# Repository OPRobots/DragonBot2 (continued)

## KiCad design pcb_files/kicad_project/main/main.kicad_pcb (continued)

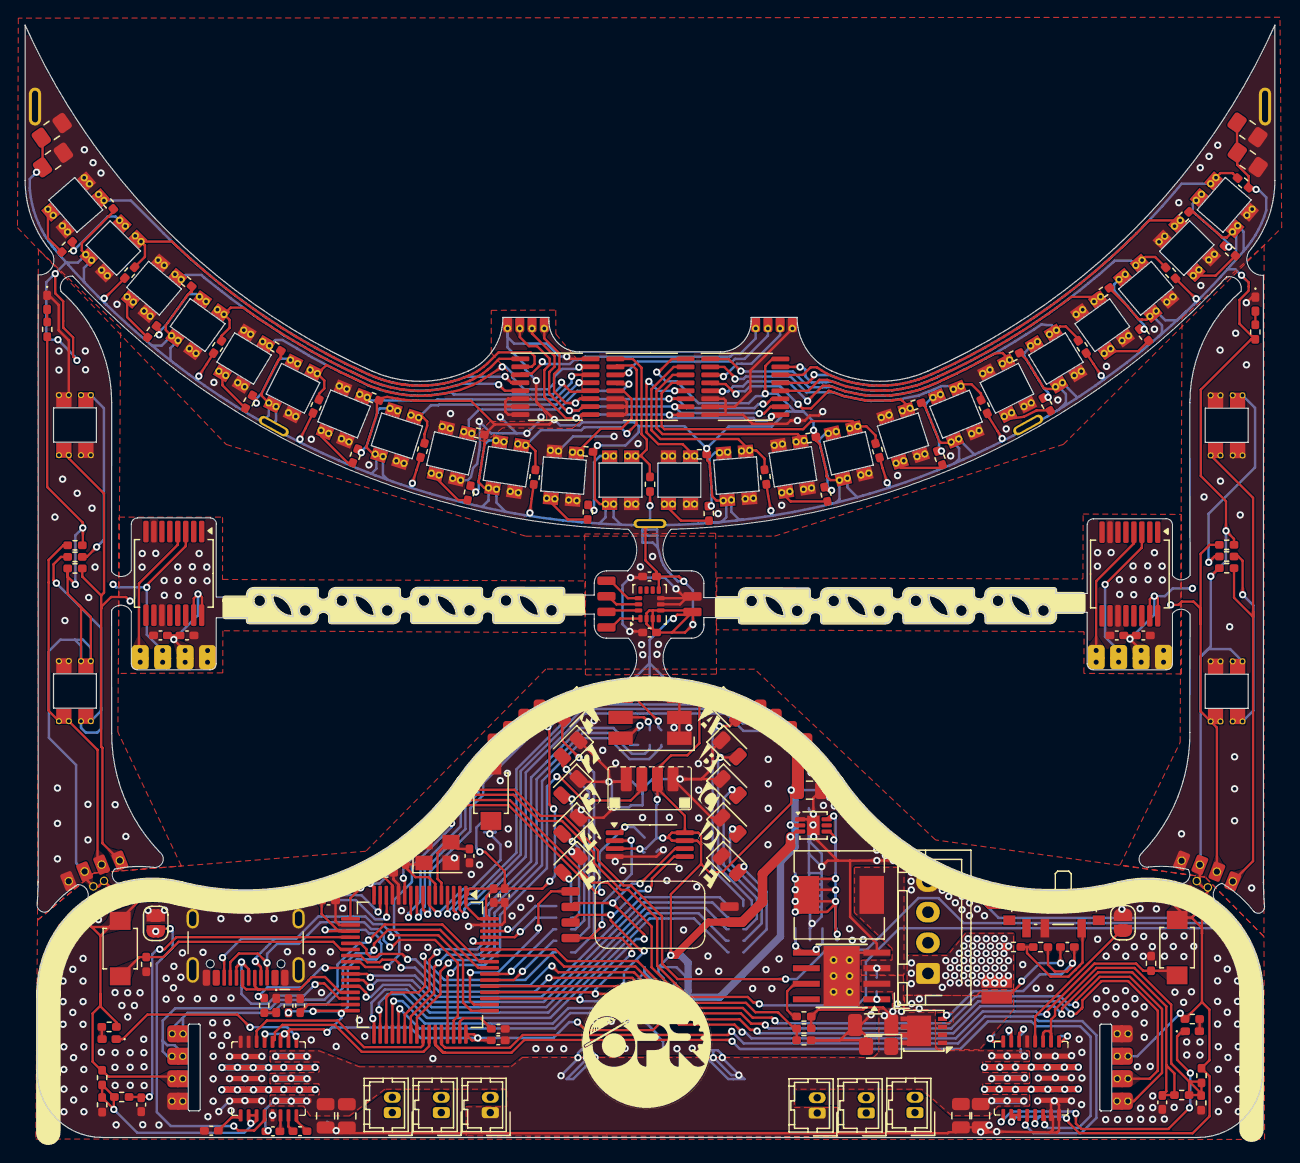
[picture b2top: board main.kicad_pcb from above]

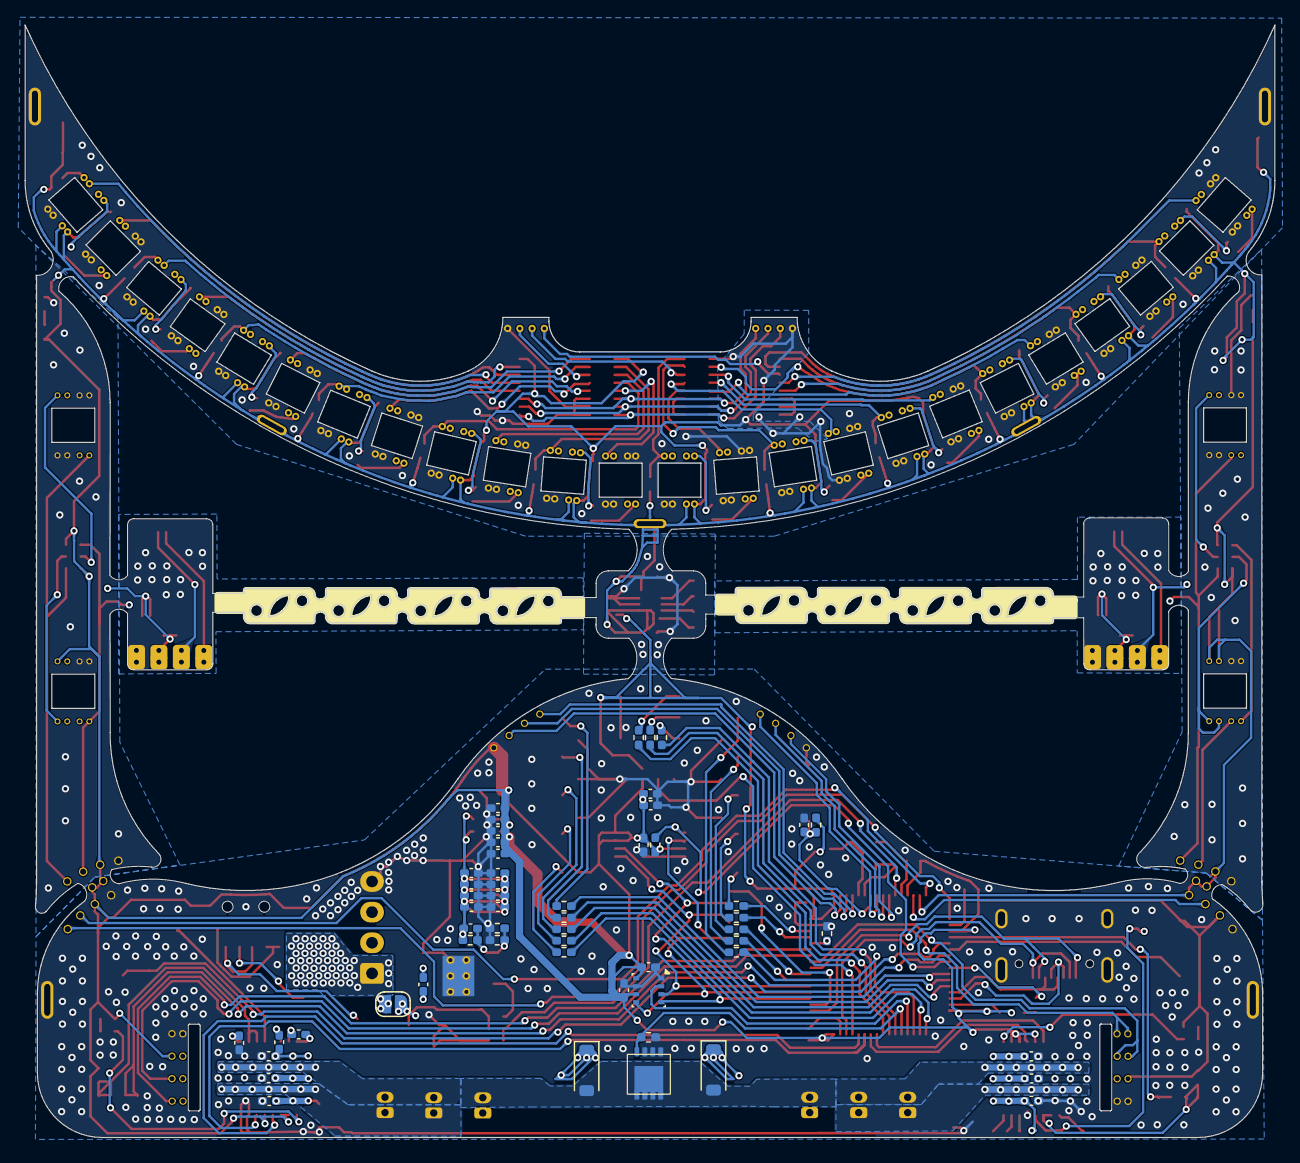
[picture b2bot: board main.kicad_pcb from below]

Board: 2 copper layers, 102.0 x 90.8 mm, 250 parts (56 on the bottom side), 186 nets.

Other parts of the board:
JP99: SolderJumper_2_Open; SolderJumper-2_P1.3mm_Open_RoundedPad1.0x1.5mm
kibuzzard-6A86F9E9: G***; kibuzzard-6A86F9E9
kibuzzard-6A86F9FA: G***; kibuzzard-6A86F9FA
kibuzzard-6A86FA0A: G***; kibuzzard-6A86FA0A
kibuzzard-6A86FA24: G***; kibuzzard-6A86FA24
kibuzzard-6A86FA32: G***; kibuzzard-6A86FA32
kibuzzard-6A86FBBC: G***; kibuzzard-6A86FBBC
kibuzzard-6A86FBC4: G***; kibuzzard-6A86FBC4
kibuzzard-6A86FBCD: G***; kibuzzard-6A86FBCD
kibuzzard-6A86FBEE: G***; kibuzzard-6A86FBEE
kibuzzard-6A86FBF6: G***; kibuzzard-6A86FBF6

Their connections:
/3.3_MPU: JP99.1 (A); also elsewhere on the board

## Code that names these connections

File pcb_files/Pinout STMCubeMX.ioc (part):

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Mcu.Name=STM32F405RGTx
Mcu.Package=LQFP64
Mcu.UserName=STM32F405RGTx
PA0-WKUP.GPIOParameters=GPIO_Label
PA0-WKUP.GPIO_Label=IN_MARK_L1
PA0-WKUP.Signal=ADCx_IN0
PA1.GPIOParameters=GPIO_Label
PA1.GPIO_Label=IN_MARK_L2
PA1.Signal=ADCx_IN1
PA10.GPIOParameters=GPIO_Label
PA10.GPIO_Label=PWM_MOT_L_B
PA10.Signal=S_TIM1_CH3
PA11.GPIOParameters=GPIO_Label
PA11.GPIO_Label=PWM_MOT_L_A
PA11.Signal=S_TIM1_CH4
PA12.GPIOParameters=GPIO_Label
PA12.GPIO_Label=IR_SENSOR
PA12.Signal=GPXTI12
PA13.Signal=SYS_JTMS-SWDIO
PA14.Signal=SYS_JTCK-SWCLK
PA15.GPIOParameters=GPIO_Label
PA15.GPIO_Label=SPI_NSS_MPU
PA15.Signal=GPIO_Output
PA2.GPIOParameters=GPIO_Label
PA2.GPIO_Label=IN_MARK_L3
PA2.Signal=ADCx_IN2
PA3.GPIOParameters=GPIO_Label
PA3.GPIO_Label=IN_MARK_R1
PA3.Signal=ADCx_IN3
PA4.GPIOParameters=GPIO_Label
PA4.GPIO_Label=IN_MARK_R2
PA4.Signal=ADCx_IN4
PA5.GPIOParameters=GPIO_Label
PA5.GPIO_Label=IN_MARK_R3
PA5.Signal=ADCx_IN5
PA6.GPIOParameters=GPIO_Label
PA6.GPIO_Label=IN_CURR_ML
PA6.Signal=ADCx_IN6
PA7.GPIOParameters=GPIO_Label
PA7.GPIO_Label=IN_CURR_MR
PA7.Signal=ADCx_IN7
PA8.GPIOParameters=GPIO_Label
PA8.GPIO_Label=PWM_MOT_R_B
PA8.Signal=S_TIM1_CH1
PA9.GPIOParameters=GPIO_Label
PA9.GPIO_Label=PWM_MOT_R_A
PA9.Signal=S_TIM1_CH2
PB0.GPIOParameters=GPIO_Label
PB0.GPIO_Label=LED_8
PB0.Signal=GPIO_Output
PB1.GPIOParameters=GPIO_Label
PB1.GPIO_Label=LED_9
PB1.Signal=GPIO_Output
PB10.Mode=Asynchronous
PB10.Signal=USART3_TX
PB11.Mode=Asynchronous
PB11.Signal=USART3_RX
PB12.GPIOParameters=GPIO_Label
PB12.GPIO_Label=LED_7
PB12.Signal=GPIO_Output
PB13.GPIOParameters=GPIO_Label
PB13.GPIO_Label=LED_6
PB13.Signal=GPIO_Output
PB14.GPIOParameters=GPIO_Label
PB14.GPIO_Label=LED_5
PB14.Signal=GPIO_Output
PB15.GPIOParameters=GPIO_Label
PB15.GPIO_Label=SPI_NSS_BAR
PB15.Signal=GPIO_Output
PB2.GPIOParameters=GPIO_Label
PB2.GPIO_Label=LED_10
PB2.Signal=GPIO_Output
PB3.GPIOParameters=GPIO_Label
PB3.GPIO_Label=LED_3
PB3.Signal=GPIO_Output
PB4.GPIOParameters=GPIO_Label
PB4.GPIO_Label=ENC_R_B
PB4.Signal=S_TIM3_CH1
PB5.GPIOParameters=GPIO_Label
PB5.GPIO_Label=ENC_R_A
PB5.Signal=S_TIM3_CH2
PB6.GPIOParameters=GPIO_Label
PB6.GPIO_Label=ENC_L_B
PB6.Signal=S_TIM4_CH1
PB7.GPIOParameters=GPIO_Label
PB7.GPIO_Label=ENC_L_A
PB7.Signal=S_TIM4_CH2
PB8.GPIOParameters=GPIO_Label
PB8.GPIO_Label=LED_2
PB8.Signal=GPIO_Output
PB9.GPIOParameters=GPIO_Label
PB9.GPIO_Label=LED_1
PB9.Signal=GPIO_Output
PC0.GPIOParameters=GPIO_Label
PC0.GPIO_Label=IN_LIN_A
PC0.Signal=ADCx_IN10
PC1.GPIOParameters=GPIO_Label
PC1.GPIO_Label=IN_LIN_B
PC1.Signal=ADCx_IN11
PC10.GPIOParameters=GPIO_Label
PC10.GPIO_Label=SPI_SCK
PC10.Mode=Full_Duplex_Master
PC10.Signal=SPI3_SCK
PC11.GPIOParameters=GPIO_Label
PC11.GPIO_Label=SPI_MISO
PC11.Mode=Full_Duplex_Master
PC11.Signal=SPI3_MISO
PC12.GPIOParameters=GPIO_Label
PC12.GPIO_Label=SPI_MOSI
PC12.Mode=Full_Duplex_Master
PC12.Signal=SPI3_MOSI
PC13-ANTI_TAMP.GPIOParameters=GPIO_Label
PC13-ANTI_TAMP.GPIO_Label=OUT_MUX_A
PC13-ANTI_TAMP.Signal=GPIO_Output
PC14-OSC32_IN.GPIOParameters=GPIO_Label
PC14-OSC32_IN.GPIO_Label=OUT_MUX_B
PC14-OSC32_IN.Signal=GPIO_Output
PC15-OSC32_OUT.GPIOParameters=GPIO_Label
PC15-OSC32_OUT.GPIO_Label=OUT_MUX_C
PC15-OSC32_OUT.Signal=GPIO_Output
PC2.GPIOParameters=GPIO_Label
PC2.GPIO_Label=IN_LIN_C
PC2.Signal=ADCx_IN12
PC3.GPIOParameters=GPIO_Label
PC3.GPIO_Label=BATT_VOLTAGE
PC3.Signal=ADCx_IN13
PC4.GPIOParameters=GPIO_Label
PC4.GPIO_Label=AUX
PC4.Signal=GPIO_Output
PC5.GPIOParameters=GPIO_Label
PC5.GPIO_Label=LED_MENU
PC5.Signal=GPIO_Output
PC6.GPIOParameters=GPIO_Label
PC6.GPIO_Label=PWM_SUC
PC6.Signal=S_TIM8_CH1
PC7.GPIOParameters=GPIO_Label
PC7.GPIO_Label=PWM_RGB_B
PC7.Signal=S_TIM8_CH2
PC8.GPIOParameters=GPIO_Label
PC8.GPIO_Label=PWM_RGB_G
PC8.Signal=S_TIM8_CH3
PC9.GPIOParameters=GPIO_Label
PC9.GPIO_Label=PWM_RGB_R
PC9.Signal=S_TIM8_CH4
PD2.GPIOParameters=GPIO_Label
PD2.GPIO_Label=LED_4
PD2.Signal=GPIO_Output
PH0-OSC_IN.Signal=RCC_OSC_IN
PH1-OSC_OUT.Signal=RCC_OSC_OUT
RCC.HSE_VALUE=25000000
RCC.SYSCLKFreq_VALUE=16000000
board=custom

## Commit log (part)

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2025-11-26 Añade esqueleto del repo
2025-11-26 Añade pinout inicial de STMCubeMX
2025-11-26 Añade proyectos de kicad
2025-11-26 Actualiza nomenclatura de pinout
2025-12-22 Comienza a hacer el esquematico de la PCB
2026-01-10 Finaliza primera version de esquematico y comienza la PCB
2026-02-10 Añade port de software de FujitoraBot2 y ZoroBot3
2026-02-10 Mejora guardado de calibración de MPU en EEPROM
2026-02-10 Mejora calibración y gestión de sensores
2026-02-24 Elimina la carpeta Sensors y su submodulo de custom_libraries
2026-02-24 "Finaliza" (CREO) la PCB main de DragonBot2
2026-02-24 Añade la PCB del chasis y revisa ajustes finales en la PCB main.
2026-04-05 Actualiza los archivos de la PCB a la ultima version pedida.
2026-04-07 Añade cambios de @robotaleh para el testeo inicial de la PCB.
